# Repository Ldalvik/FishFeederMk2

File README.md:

# FishFeederMk2
Rework of Biotech fishfeeder

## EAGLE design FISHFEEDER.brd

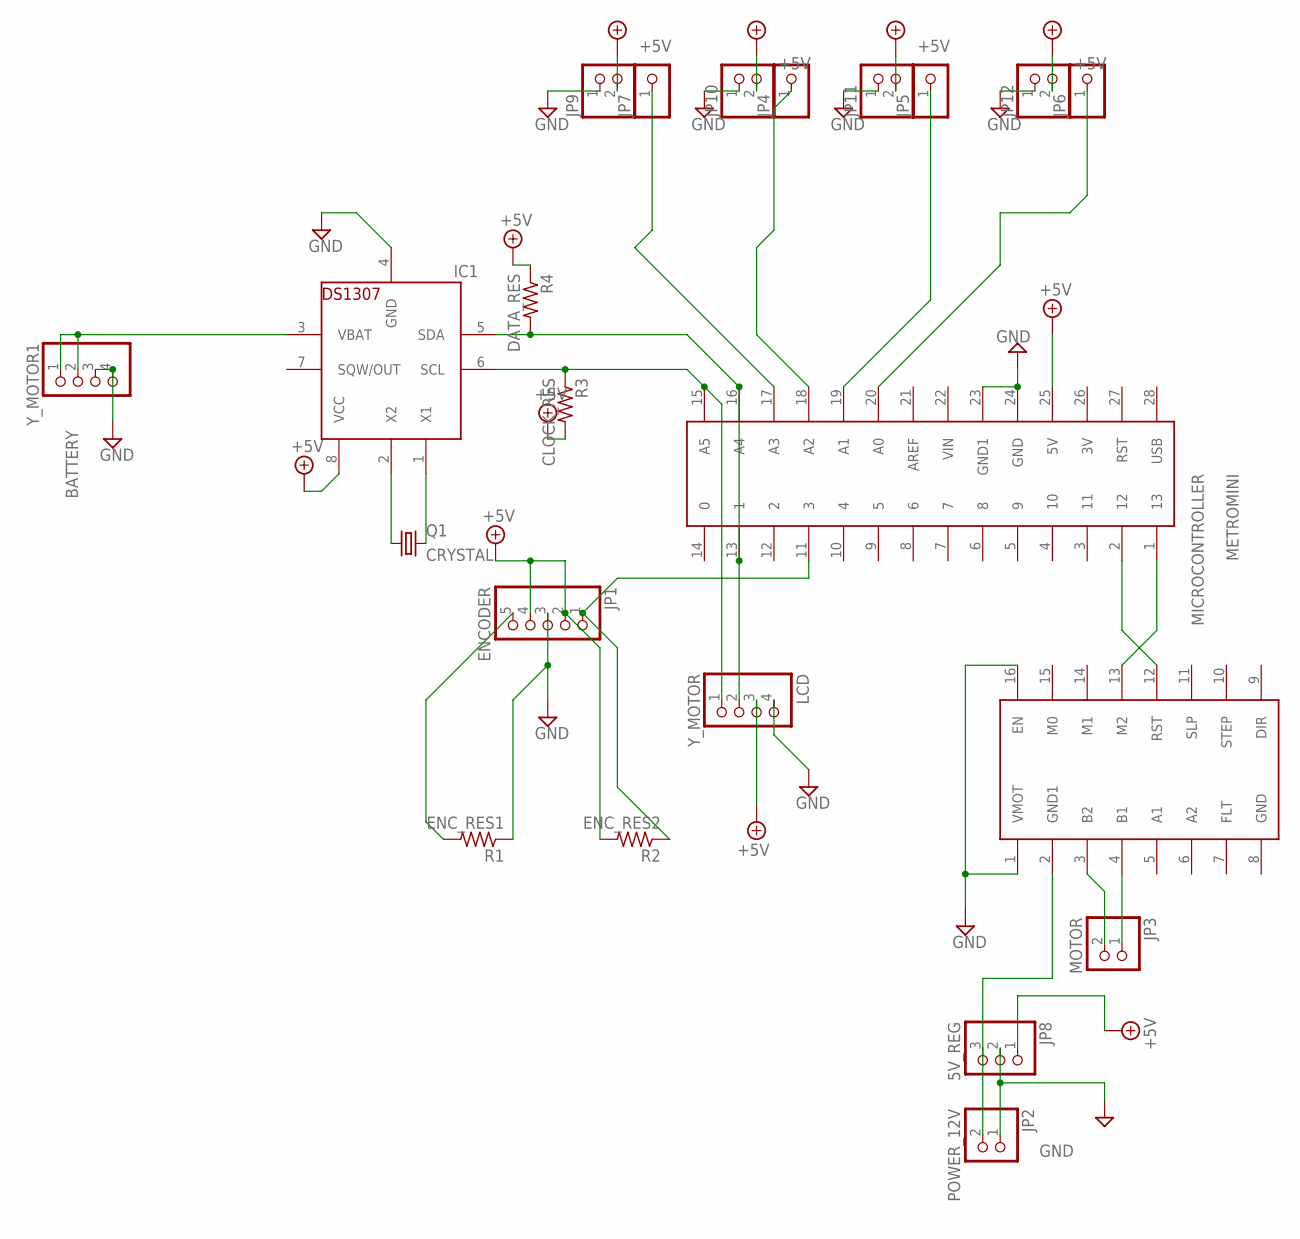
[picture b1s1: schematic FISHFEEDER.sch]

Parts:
IC1: CLOCK_CHIP; DIL08
JP1: ENCODER; 1X05
JP2: POWER_12V; 1X02
JP3: MOTOR; 1X02
JP4, JP5, JP6, JP7: PINHD-1X1CB; 1X01-CLEANBIG
JP8: 5V_REG; 1X03
JP9, JP10, JP11, JP12: PINHD-1X2; 1X02
MICROCONTROLLER: METROMINI
Q1: CRYSTAL; TC26H
R1: ENC_RES1; 0204/7
R2: ENC_RES2; 0204/7
R3: CLOCK_RES; 0204/7
R4: DATA_RES; 0204/7
U$1: DRV8825
Y_MOTOR: LCD; 1X04
Y_MOTOR1: BATTERY; 1X04

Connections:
12V: JP2.2, JP8.3, U$1.2 (GND1)
+5V: IC1.8 (VCC), JP1.2, JP1.4, JP8.1, JP9.2, JP10.2, JP11.2, JP12.2, MICROCONTROLLER.25 (5V), R2.2, R3.2, R4.1, Y_MOTOR.3
ENC_DATA: JP1.1, MICROCONTROLLER.11 (3), R2.1
GND: IC1.4 (GND), JP1.3, JP2.1, JP8.2, JP9.1, JP10.1, JP11.1, JP12.1, MICROCONTROLLER.23 (GND1), MICROCONTROLLER.24 (GND), R1.1, U$1.1 (VMOT), U$1.16 (EN), Y_MOTOR.4, Y_MOTOR1.3, Y_MOTOR1.4
unnamed: IC1.5 (SDA), MICROCONTROLLER.13 (1), MICROCONTROLLER.16 (A4), R4.2, Y_MOTOR.2
unnamed: IC1.6 (SCL), MICROCONTROLLER.15 (A5), R3.1, Y_MOTOR.1
unnamed: IC1.2 (X2), Q1.1
unnamed: IC1.1 (X1), Q1.2
unnamed: IC1.3 (VBAT), Y_MOTOR1.1, Y_MOTOR1.2
unnamed: MICROCONTROLLER.2 (12), U$1.12 (RST)
unnamed: JP6.1, MICROCONTROLLER.20 (A0)
unnamed: JP5.1, MICROCONTROLLER.19 (A1)
unnamed: JP4.1, MICROCONTROLLER.18 (A2)
unnamed: JP7.1, MICROCONTROLLER.17 (A3)
unnamed: JP1.5, R1.2
unnamed: MICROCONTROLLER.1 (13), U$1.13 (M2)
unnamed: JP3.2, U$1.3 (B2)
unnamed: JP3.1, U$1.4 (B1)

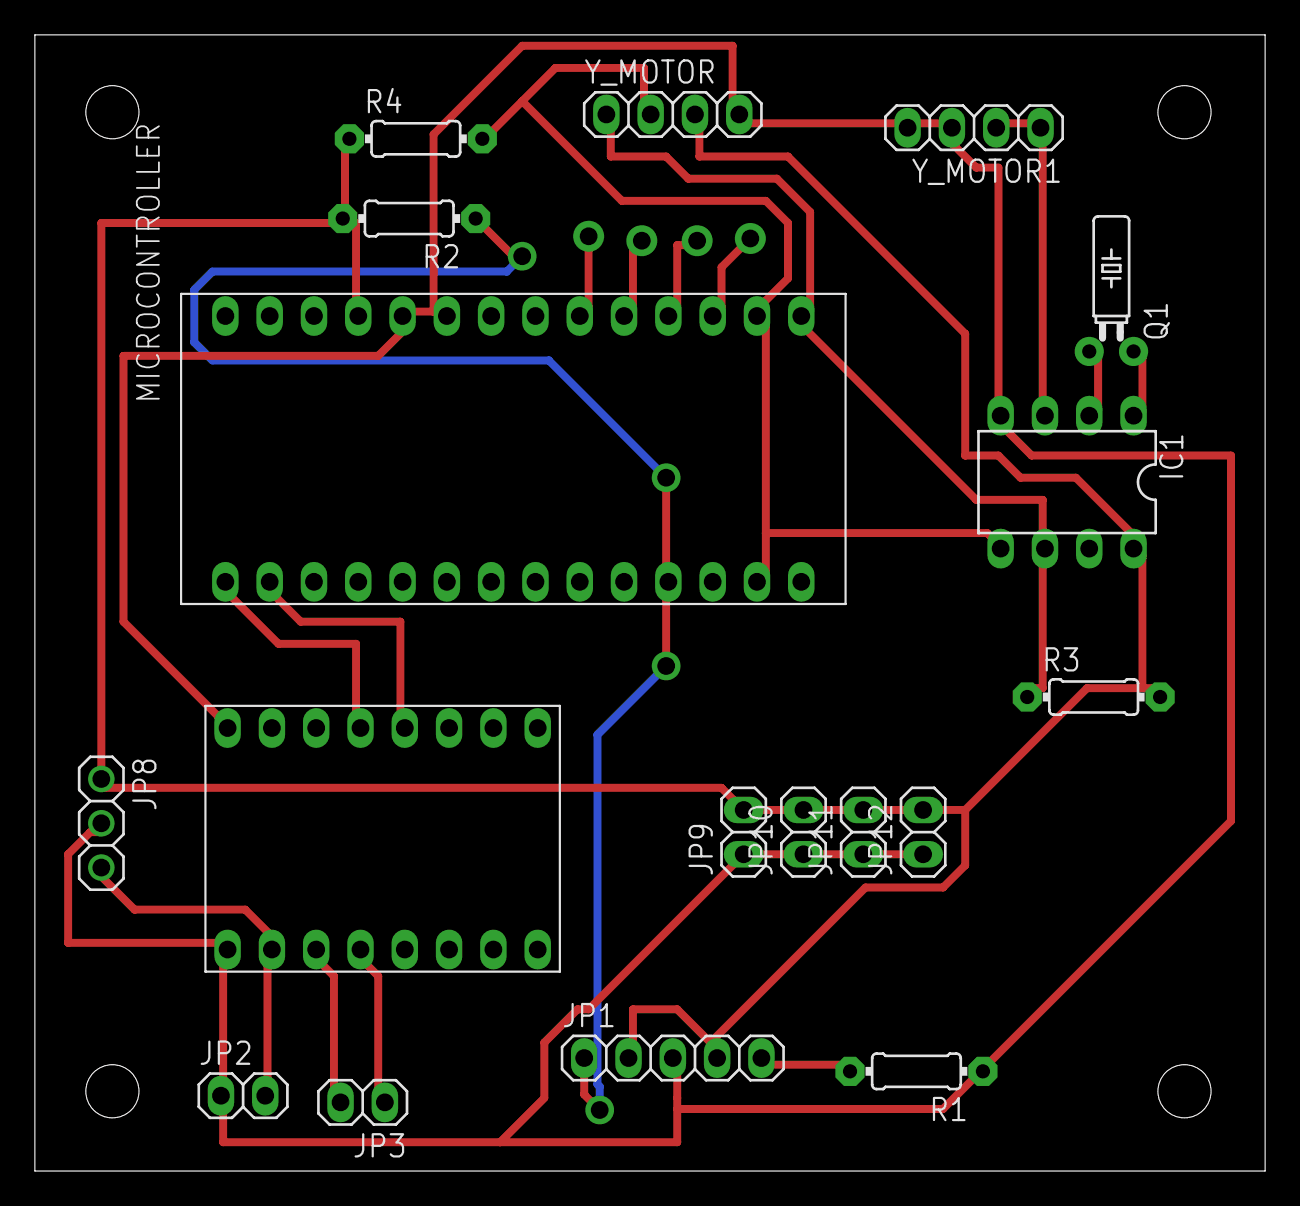
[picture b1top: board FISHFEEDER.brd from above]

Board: 2 copper layers, 70.5 x 65.1 mm, 22 parts (0 on the bottom side), 18 nets.
